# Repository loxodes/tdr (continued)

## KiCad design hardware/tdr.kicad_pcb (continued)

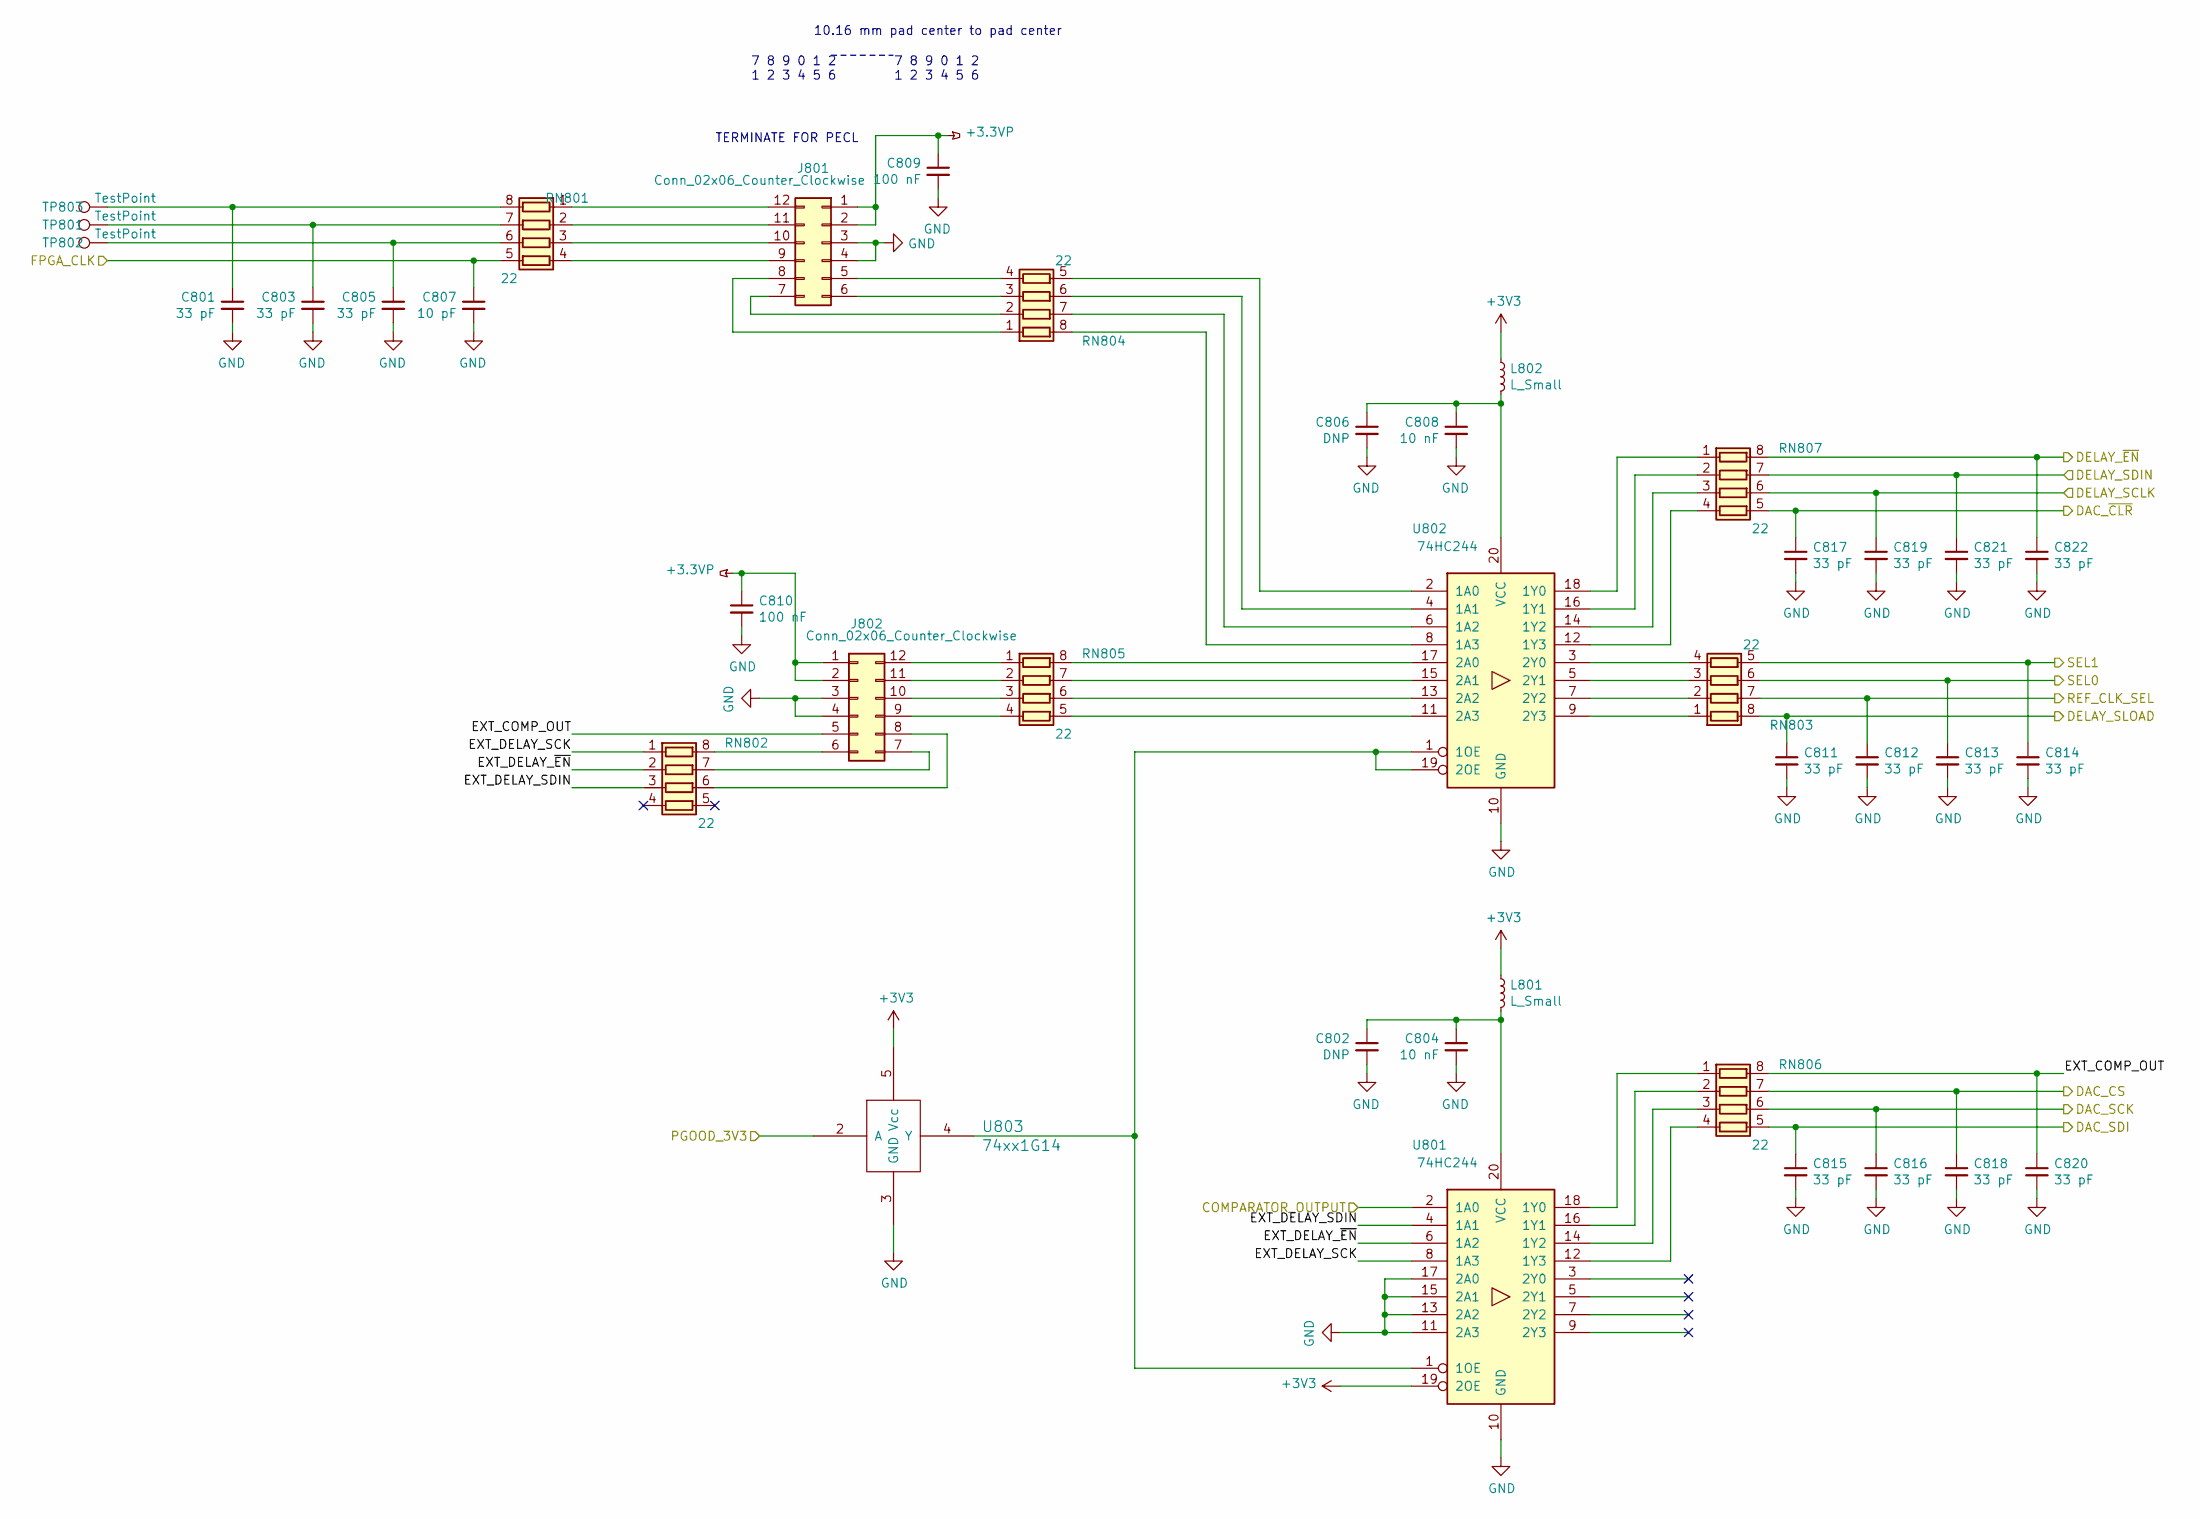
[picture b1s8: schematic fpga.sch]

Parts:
C801, C803, C805, C811, C812, C813, C814, C815, C816, C817, C818, C819, C820, C821, C822: 33 pF; C_0402
C802, C806: DNP; C_0603
C804, C808: 10 nF; C_0402
C807: 10 pF; C_0402
C809, C810: 100 nF; C_0402
J801, J802: Conn_02x06_Counter_Clockwise; Pin_Header_Angled_2x06
L801, L802: L_Small; R_0402
RN801, RN802, RN803, RN804, RN805, RN806, RN807: 22; R_Array_Convex_4x0402
TP801, TP802, TP803: TestPoint; TP07R
U801, U802: 74HC244; TSSOP-20_4.4x6.5mm_Pitch0.65mm
U803: 74xx1G14; SOT-23-5

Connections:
+3.3VP: C809.1, C810.1, J801.1, J801.2, J802.1, J802.2
+3V3: L801.1, L802.1, U801.19 (2OE), U803.5 (Vcc); also elsewhere on the board
/COMPARATOR_OUTPUT: U801.2 (1A0); also elsewhere on the board
/PGOOD_3V3: U803.2 (A); also elsewhere on the board
/clock/CLK_FPGA: C807.1, RN801.5 (R4.2); also elsewhere on the board
/clock/CLK_SEL: C812.1, RN803.7 (R2.2); also elsewhere on the board
/fpga_connector/DAC_CS: C818.1, RN806.7 (R2.2); also elsewhere on the board
/fpga_connector/DAC_SCK: C816.1, RN806.6 (R3.2); also elsewhere on the board
/fpga_connector/DAC_SDI: C815.1, RN806.5 (R4.2); also elsewhere on the board
/fpga_connector/DAC_~CLR: C817.1, RN807.5 (R4.2); also elsewhere on the board
/fpga_connector/DELAY_SCLK: C819.1, RN807.6 (R3.2); also elsewhere on the board
/fpga_connector/DELAY_SDIN: C821.1, RN807.7 (R2.2); also elsewhere on the board
/fpga_connector/DELAY_SLOAD: C811.1, RN803.8 (R1.2); also elsewhere on the board
/fpga_connector/DELAY_~EN: C822.1, RN807.8 (R1.2); also elsewhere on the board
/fpga_connector/EXT_COMP_OUT: C820.1, J802.5, RN806.8 (R1.2)
/fpga_connector/EXT_DELAY_SCK: RN802.1 (R1.1), U801.8 (1A3)
/fpga_connector/EXT_DELAY_SDIN: RN802.3 (R3.1), U801.4 (1A1)
/fpga_connector/EXT_DELAY_~EN: RN802.2 (R2.1), U801.6 (1A2)
/fpga_connector/SEL0: C813.1, RN803.6 (R3.2); also elsewhere on the board
/fpga_connector/SEL1: C814.1, RN803.5 (R4.2); also elsewhere on the board
GND: C801.2, C802.2, C803.2, C804.2, C805.2, C806.2, C807.2, C808.2, C809.2, C810.2, C811.2, C812.2, C813.2, C814.2, C815.2, C816.2, C817.2, C818.2, C819.2, C820.2, C821.2, C822.2, J801.3, J801.4, J802.3, J802.4, U801.10 (GND), U801.11 (2A3), U801.13 (2A2), U801.15 (2A1), U801.17 (2A0), U802.10 (GND), U803.3 (GND); also elsewhere on the board
unnamed: C801.1, RN801.8 (R1.2), TP803.1
unnamed: C802.1, C804.1, L801.2, U801.20 (VCC)
unnamed: C803.1, RN801.7 (R2.2), TP801.1
unnamed: C805.1, RN801.6 (R3.2), TP802.1
unnamed: C806.1, C808.1, L802.2, U802.20 (VCC)
unnamed: J801.5, RN804.4 (R4.1)
unnamed: J801.6, RN804.3 (R3.1)
unnamed: J801.7, RN804.2 (R2.1)
unnamed: J801.8, RN804.1 (R1.1)
unnamed: J801.9, RN801.4 (R4.1)
unnamed: J801.10, RN801.3 (R3.1)
unnamed: J801.11, RN801.2 (R2.1)
unnamed: J801.12, RN801.1 (R1.1)
unnamed: J802.6, RN802.8 (R1.2)
unnamed: J802.7, RN802.7 (R2.2)
unnamed: J802.8, RN802.6 (R3.2)
unnamed: J802.9, RN805.4 (R4.1)
unnamed: J802.10, RN805.3 (R3.1)
unnamed: J802.11, RN805.2 (R2.1)
unnamed: J802.12, RN805.1 (R1.1)
unnamed: RN803.1 (R1.1), U802.9 (2Y3)
unnamed: RN803.2 (R2.1), U802.7 (2Y2)
unnamed: RN803.3 (R3.1), U802.5 (2Y1)
unnamed: RN803.4 (R4.1), U802.3 (2Y0)
unnamed: RN804.5 (R4.2), U802.2 (1A0)
unnamed: RN804.6 (R3.2), U802.4 (1A1)
unnamed: RN804.7 (R2.2), U802.6 (1A2)
unnamed: RN804.8 (R1.2), U802.8 (1A3)
unnamed: RN805.5 (R4.2), U802.11 (2A3)
unnamed: RN805.6 (R3.2), U802.13 (2A2)
unnamed: RN805.7 (R2.2), U802.15 (2A1)
unnamed: RN805.8 (R1.2), U802.17 (2A0)
unnamed: RN806.1 (R1.1), U801.18 (1Y0)
unnamed: RN806.2 (R2.1), U801.16 (1Y1)
unnamed: RN806.3 (R3.1), U801.14 (1Y2)
unnamed: RN806.4 (R4.1), U801.12 (1Y3)
unnamed: RN807.1 (R1.1), U802.18 (1Y0)
unnamed: RN807.2 (R2.1), U802.16 (1Y1)
unnamed: RN807.3 (R3.1), U802.14 (1Y2)
unnamed: RN807.4 (R4.1), U802.12 (1Y3)
unnamed: U801.1 (1OE), U802.1 (1OE), U802.19 (2OE), U803.4 (Y)

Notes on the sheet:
TERMINATE FOR PECL
7 8 9 0 1 2 1 2 3 4 5 6
10.16 mm pad center to pad center

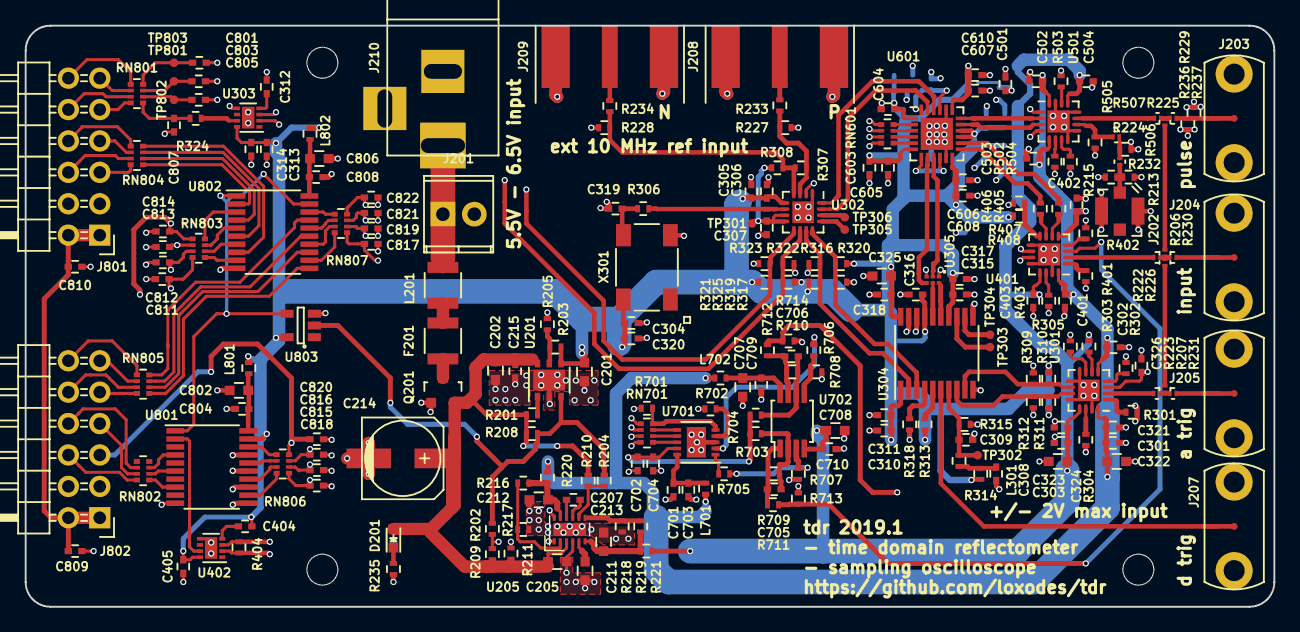
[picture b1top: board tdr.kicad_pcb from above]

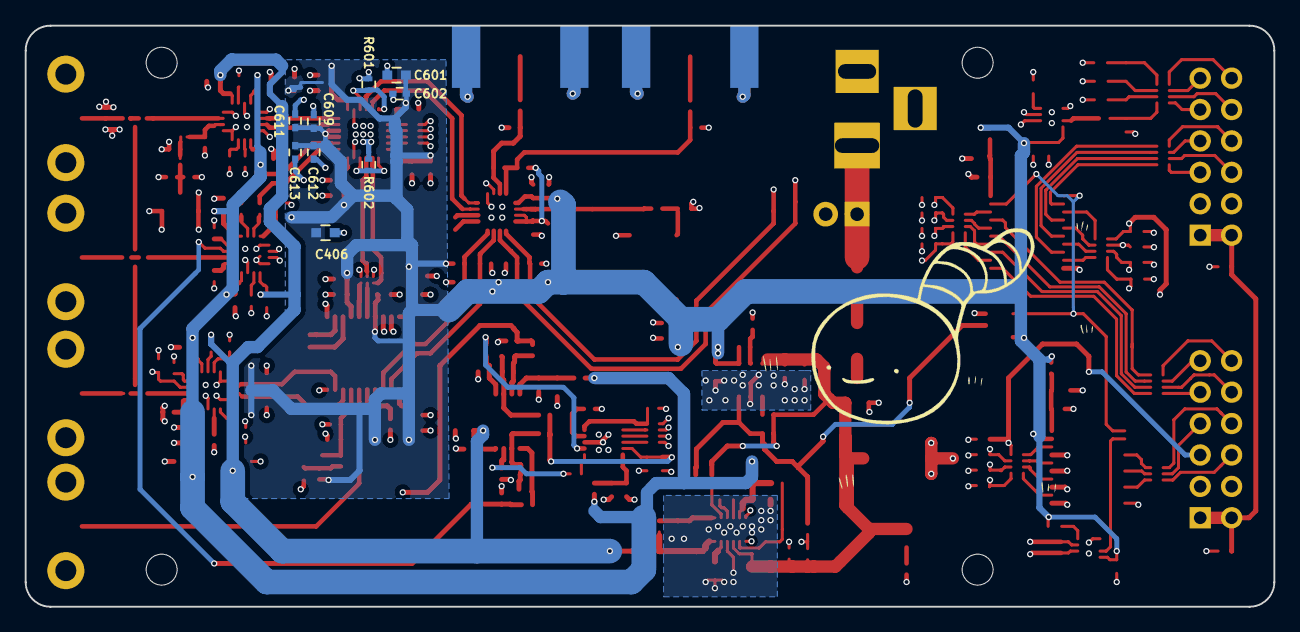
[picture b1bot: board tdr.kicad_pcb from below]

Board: 4 copper layers, 101.0 x 47.0 mm, 239 parts (9 on the bottom side), 170 nets.

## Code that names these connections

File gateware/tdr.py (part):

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        ("comp_in", 0, Pins("J3:14")),
        ("start_sweep", 0, Pins("J3:0")),
        ("delay_sck", 0, Pins("J3:1")),
        ("delay_en", 0, Pins("J3:2")),
        ("delay_sdin", 0, Pins("J3:3")),
        ("delay_sload", 0, Pins("J3:4")),
        ("trig_sel0", 0, Pins("J3:5")),
        ("trig_sel1", 0, Pins("J3:6")),
        ("ref_sel", 0, Pins("J3:7")),
        ("dac_clr", 0, Pins("J3:9")),
        ("dac_cs", 0, Pins("J3:10")),
        ("dac_sck", 0, Pins("J3:11")),
        ("dac_sdi", 0, Pins("J3:12")),
        ("uart_tx", 0, Pins("J3:13")),
        ("uart_rx", 0, Pins("J3:15")),
        ("clk_in", 0, Pins("J3:16")),
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
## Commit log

2018-11-02 inital commit of tdr project, schematic in progress
2018-11-03 more work on tdr schematic
2018-12-09 work on tdr schematic..
2018-12-09 footprint assignment
2018-12-16 work on schematic..
2018-12-29 work on tdr component placement
2018-12-31 more component placement on tdr..
2018-12-31 added rf crossover for latch trigger line to help with layout
2019-01-02 finished first pass component placement and drc setup, swapped digital pins for easier routing
2019-01-02 added draft block diagrams
2019-01-05 layout of low speed digital traces
2019-01-05 layout of low speed analog and power sections
2019-01-05 routing high speed digital
2019-01-06 more layout.. 28 unrouted nets to go
2019-01-06 first pass of layout complete
2019-01-06 cleanup of tdr layout
2019-01-07 fixed CML termination.. ready to order?
2019-01-07 schematic cleanup, BOM consolidation
2019-01-10 added interactive BOM for manual component placement
2019-01-10 clean up of interactive BOM page, waiting on PCBs
2019-01-31 added picture of assembled pcb, started erratum for r0..
2019-02-07 started software scraps to test TDR
2019-02-08 assigned pins for tdr beaglebone bitbang driver
2019-02-10 fix a bunch of software bugs..
2019-02-10 improve PMOD connector pin labels in schematic..
2019-02-21 tdr software is working!
2019-02-21 fixed U401 and U601 output termination, tdr works, added first sweep of output pulse to README
2019-02-21 added missing plot of the first sweep from the TDR
2019-02-21 fix README formatting
2019-02-21 updated tdr picture to show bodge wires, added r0 schematic pdf export
2019-02-28 fix crossover distortion on analog triggered measurements
2019-02-28 40x speedup in scope sweep speed - binary search for voltage instead of brute force
2019-02-28 updated readme, added analog sweep
2019-03-08 added in progress and incomplete migen port of the TDR control software
2019-03-21 work on delay and dac drivers
2019-03-25 work on top level tdr controller
2019-03-27 added pin mapping to tdr.py
2019-03-28 add testbench for tdr gateware
2019-03-29 added programming to tdr.py
2019-04-05 cleanup tdr code, add scope state for testing digital outputs
2019-04-07 let dac settle before reading off comparator
2019-04-07 added startup delay before configuring dac, sped up uart
2019-04-08 tdr sorta working, bypass dac a
2019-04-14 fpga tdr control works... for every other sample?
2019-04-14 tdr gateware works - run fpga clock off sample clock..
2019-04-14 use all 12 bits of vertical resolution with fpga, added plot of falling edge of tdr
2019-04-14 fix readme to point to newer scope capture
2019-04-14 updated readme with new sampling rate
2019-04-16 added data from test sweeps
2019-04-26 added impedance plot, updated schematic with errata
